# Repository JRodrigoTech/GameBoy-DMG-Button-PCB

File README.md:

# Game Boy DMG Button Breakout PCB

## Where to buy :package:
- [On my **Tindie** Store](http://tindie.jrodrigo.net)

## License
#### Licenced under [Creative Commons - Attribution and Share Alike](https://github.com/JRodrigoTech/GameBoy-DMG-Button-PCB/blob/master/LICENSE.md) by [J.Rodrigo](http://www.jrodrigo.net)

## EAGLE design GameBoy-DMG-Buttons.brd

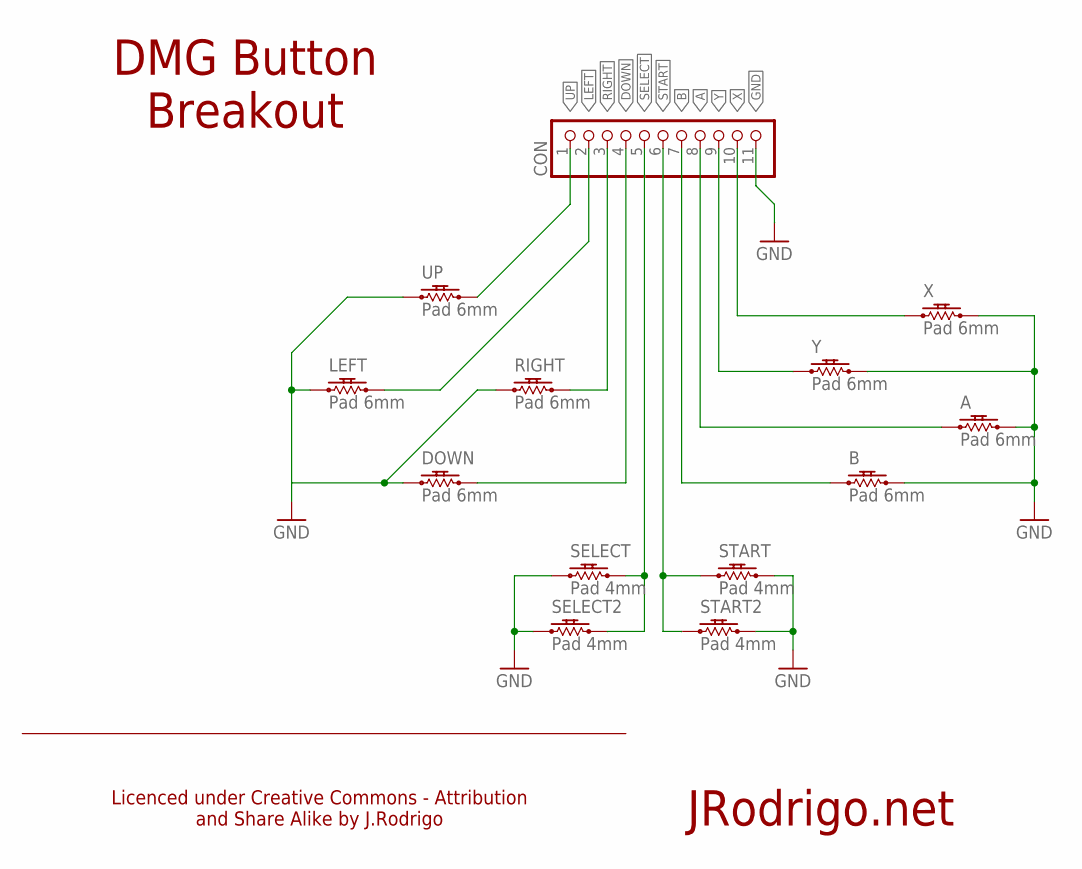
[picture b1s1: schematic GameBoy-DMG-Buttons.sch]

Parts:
A: Pad 6mm; BUTTON_PAD-D6MM
B: Pad 6mm; BUTTON_PAD-D6MM
CON: PINHD-1X11; 1X11
DOWN: Pad 6mm; BUTTON_PAD-D6MM
LEFT: Pad 6mm; BUTTON_PAD-D6MM
RIGHT: Pad 6mm; BUTTON_PAD-D6MM
SELECT, SELECT2: Pad 4mm; BUTTON_PAD-D4MM
START, START2: Pad 4mm; BUTTON_PAD-D4MM
UP: Pad 6mm; BUTTON_PAD-D6MM
X: Pad 6mm; BUTTON_PAD-D6MM
Y: Pad 6mm; BUTTON_PAD-D6MM

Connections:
A: A.P1 (1), CON.8
B: B.P1 (1), CON.7
DOWN: CON.4, DOWN.P2 (2)
GND: A.P2 (2), B.P2 (2), CON.11, DOWN.P1 (1), LEFT.P1 (1), RIGHT.P1 (1), SELECT.P1 (1), SELECT2.P1 (1), START.P2 (2), START2.P2 (2), UP.P1 (1), X.P2 (2), Y.P2 (2)
LEFT: CON.2, LEFT.P2 (2)
RIGHT: CON.3, RIGHT.P2 (2)
SELECT: CON.5, SELECT.P2 (2), SELECT2.P2 (2)
START: CON.6, START.P1 (1), START2.P1 (1)
UP: CON.1, UP.P2 (2)
X: CON.10, X.P1 (1)
Y: CON.9, Y.P1 (1)

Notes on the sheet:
JRodrigo.net
Licenced under Creative Commons - Attribution and Share Alike by J.Rodrigo
DMG Button Breakout

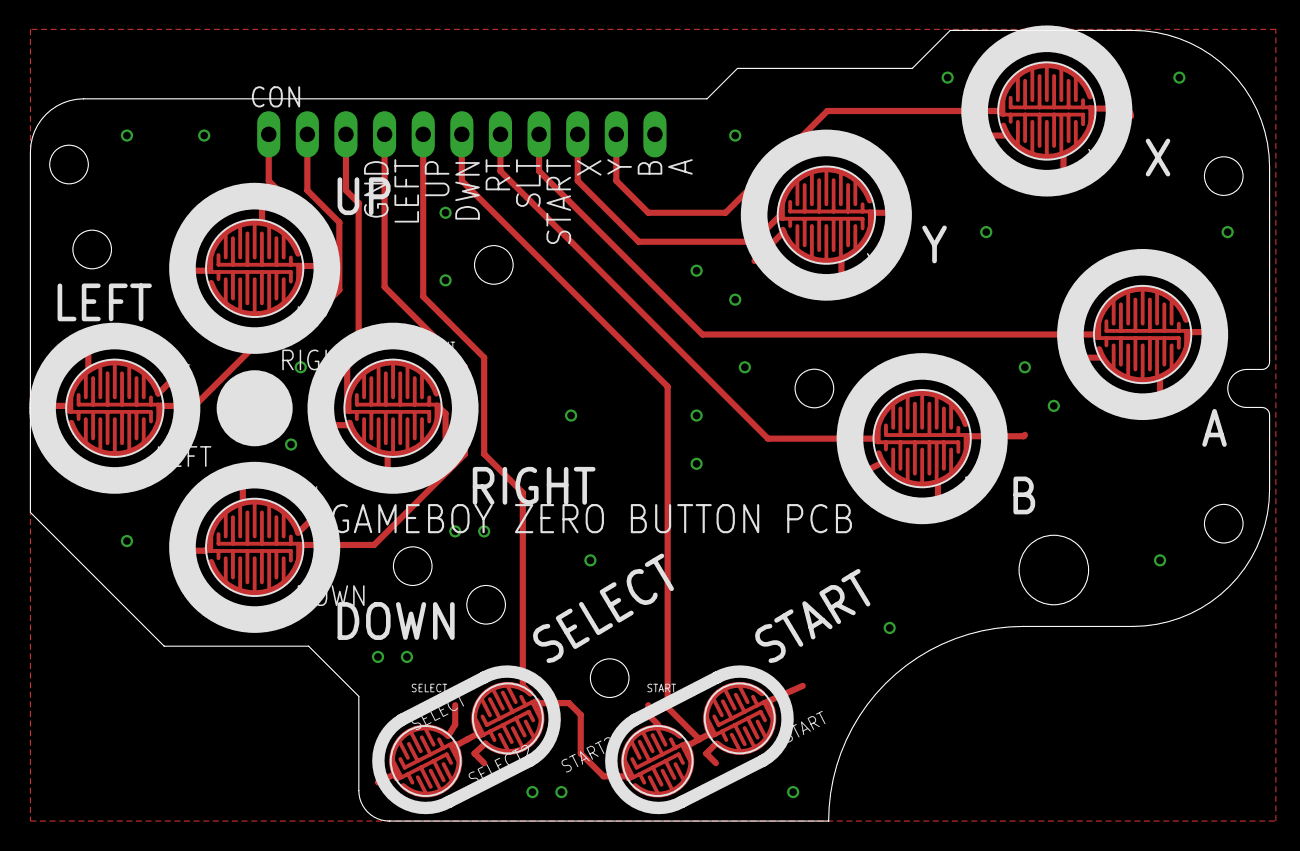
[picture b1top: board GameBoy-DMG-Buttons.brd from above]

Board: 2 copper layers, 81.5 x 52.0 mm, 13 parts (0 on the bottom side), 11 nets.

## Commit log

2017-10-28 Initial commit of LICENSE.md
2017-11-02 Initial release
2017-11-02 Initial commit of README.md
2017-11-03 Minor updates on the schematic
2017-11-03 Silkscreen fixed
2017-11-10 Fixed shorts to GND on silicone pads
2017-11-23 Button Holder - 3D print STL and SW design files

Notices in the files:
parts and their libraries:
jrodrigo: Creative Commons - Attribution and Share Alike 4.0 International - https://creativecommons.org/licenses/by-sa/4.0
